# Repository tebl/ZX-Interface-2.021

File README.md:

# ZX Interface 2.021
I woke up in the middle of the night with idea, and like most non-sensical ideas - they usually disappear in the morning. Can't remember what that idea was, but it was properly better than this one: recreating a simple version of the *ZX Interface 2* because I simply can't afford the prices the original ones are going for. Having made a few *improvements* to the original design, I was going to call it the *ZX Interface 2000* - that would however imply that I had put anything modern into it, so *ZX Interface 2.021* was the name I came up with instead. There's even a short video showing it running on [YouTube](https://youtu.be/rGyqisjjOV8).

There are other more modern implementations for putting together a ZX Spectrum cartridge solution, the Dandanator comes to mind, but I wanted something without the magic black boxes (MCUs, FPGAs or GALs) - my goal is that it should be easy to build and easy to understand. Also, I kind of like having various physical cartridges that can plug into it - so an actual cartridge slot was always a requisite for this project. 

Over to the improvements then, of which there are mainly just one that hasn't already been mentioned (the first one being the elimination of custom IC, for which there are no replacements). The other one is that logic for bank switching has been integrated into the interface, in its current state it allows you to access up to 512k ROMs in 16k segments. Four of them actually, bringing the maximum addressable ROM up to a whopping 4MB (that's 4096KB, not merely 4 Mbit).

The cartridges available mostly will have some different attributes, so you'll need to check out the README for each one of them to access all relevant information. When starting out I recommend starting with the diagnostic cartridge, it supports a single EPROM of up to 64K - giving you access to four 16K ROM images that you can switch between by using a technique called [bank switching](https://github.com/tebl/ZX-Interface-2.021/blob/main/documentation/bank_switching.md). The ZX Spectrum computer doesn't exactly expect you to hot-swap them this way, so there is a need to add a [Cartridge Loader](https://github.com/tebl/ZX-Interface-2.021/tree/main/software/cartridge_loader) program to ensure that the program starts correctly. To make things a bit easier on myself when it comes to creating cartridge compilations, I've put together a [Cartridge Creator](https://github.com/tebl/ZX-Interface-2.021/tree/main/software/cartridge_creator) that automates tasks as well as supporting updating the loader program with bank titles as well as changing out the boot screen with ZX Spectrum SCR-files.

The diagnostic software I'm using by Brendan Alford, will attempt to write state information to the LEDs on port 63. You can also play around with them directly from basic, just do an "*OUT 63, 255*" - to turn all of them on. Battlestar Galactica fans will intuitively know what tomorrows project ought to be!

The project includes a bunch of faceplates, they are mainly just there to look incredibly cool! Especially in black. While I've done a few pretty ones to match specific games, I've not obtained permission to include the likeness of any of the characters - for that reason, those have been intentionally kept separate from the github-repository. They may however show up in the gallery sections, because they exist and I had fun making them for my own personal enjoyment.

## Getting one
I don't have the capability of selling completed units or "kits" for building one, mainly due to health reasons. If you want one you will probably have to build it yourself, alternatively you could always call your favourite friend - preferably one that already owns, or is willing to buy a soldering iron of reasonable quality.

The following table will point you to more information about the specific modules, including a list of the components that goes into building one of them (referred to as a BOM). While the interface can be used as a standalone Sinclair joystick interface, you'll more than likely want at least one of the additional cartridges so that you have something to plug into it as well. Note that there will be several faceplates available for these, these as well as the PCBs for the modules listed are available on [PCBWay shared projects](https://www.pcbway.com/project/shareproject/?tag=ZX%20Interface%202.021).

| Module                      | Description                       |
| --------------------------- | --------------------------------- |
| [ZX Interface 2.021](https://github.com/tebl/ZX-Interface-2.021/tree/main/ZX%20Interface%202021) | The actual interface, includes cartridge slot and joystick interface.
| [ZX Diagnostic 2.021](https://github.com/tebl/ZX-Interface-2.021/tree/main/ZX%20Diagnostic%202021) | A diagnostic cartridge, only for use with *ZX Interface 2.021*.
| [ZX Cartridge 2.021](https://github.com/tebl/ZX-Interface-2.021/tree/main/ZX%20Cartridge%202021) | Cartridge supporting up to two 64K ROMs, eight banks of data in total. Only for use with *ZX Interface 2.021*.
| [ZX Cartridge 1.983](https://github.com/tebl/ZX-Interface-2.021/tree/main/ZX%20Cartridge%201983) | A simple cartridge that can also be used with the original ZX Interface 2 (without bank switching support).

**NB!** As with all things you're soldering together by yourself, the one who soldered it - takes responsibility for it. I'll try to help in any way that I can, but know that this is a hobby-grade project and my health is not such that I can focus on too many things at any given time. Check out the [schematic](https://github.com/tebl/ZX-Interface-2.021/tree/main/documentation/schematic) while you wait, just about every problem is just an opportunity for learning and there is a significant chance that you'll be able to find your answer within it.

## Setting it up
The *ZX Interface 2.021* has a handful of jumpers that need to be set correctly in order to keep everything working as intended (refer to image below for reference). The jumper in the top left corner is used to enable the joystick interface, put a jumper across pins 1-2 (the lower position) and it should provide you with many hours of joy with your favourite Atari-compatible stick.

The second jumper, middle right section allows you to hardcode one of the address lines used for bank switching. Setting it the lower position forces it high, in effect allowing you to quickly select between two 16k ROM images in the first and second bank - when all else fails. This is here as a way to swap between diagnostic images when the machine isn't capabable of doing this in the preferred way. In normal use, jumper across pins 1-2 (this is the upper position).

**NB!** As with all kinds of vintage electronics that you don't want to destroy, you shouldn't attempt to insert or remove a cartridge when the system is powered up. Ignoring this will either kill this interface, the cartridge or your computer - sometimes all of them.

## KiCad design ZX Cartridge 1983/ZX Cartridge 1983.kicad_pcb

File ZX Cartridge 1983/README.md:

# ZX Cartridge 1.983
With the ZX Cartridge 2.021, I intentionally created a cartridge that wouldn't be compatible with any of the original cartridge interfaces released for the ZX Spectrum. The more known of these type of interfaces is the original *ZX Interface 2*, but Kempston also released a well known one in the form of the *Kempston Pro Joystick Interface*. The first one was naturally priced firmly out of my price-range, the second one I got a hold of wasn't in a working state - so I went for option three instead, the *RAM turbo Mk2* joystick interface. Having found a working interface, I wanted an actual cartridge to use with it - so I created the *ZX Cartridge 1.983* to test things out.

True to form, I didn't simply want to build a 16K cartridge - so I sprinkled a little bit of extra feature creep upon it. I figured that I'd look into being able to use even larger EEPROMs that what I'd used so far, with the 27C020 able to hold 16 of these images - pretty extreme when considering that the system only had 10 officially released titles. There are a few [cassette conversions](http://www.fruitcake.plus.com/Sinclair/Interface2/Cartridges/Interface2_RC_New_3rdParty_GameConversions.htm) that can be used as well, good enough to fill a couple of them. With 16 images possible combinations I needed a way to choose between them, cheap as I am the solution became a 4 position DIP-switch. Just because I already had them and the space, I added a completely optional HEX-decoder IC and 7segment display - gloriously over-engineered. Smaller (E)EPROMs can still be used such as the 27C256/27C512 can still be used, you just need to install components to match.

- [1> Building the cartridge](#1-building-the-cartridge)
  - [1.1> Soldering it together](#11-soldering-it-together)
  - [1.2> Testing it out](#12-testing-it-out)
- [2> Schematic](#2-schematic)
- [3> BOM](#3-bom)

# 1> Building the cartridge
Building the unit assumes you have at least minor experience soldering things together, recommended is at least a soldering station with adjustable temperature to get started - usually you'll want some 60/40 solder tin (if you can get that where you live). Given that we're going to be flashing data onto EPROM chips, you'll need an EPROM programmer suitable for this task - the one I'm using is a MiniPro TL866CS and so far it's surpassed my expectations for such a reasonably priced device. If you are going to use EPROM chips you will need an EPROM ereaser as well, but read on - you might not need that depending on the chips you purchase.

With the equipment sorted, now comes the shopping - so head on over to the [BOM](#3-bom)-section for some information on what you need. Note that with sites such as ebay, AliExpress and similar sites that sell cheap chinese components, you'll need to treat these as a suggested search term and look for something that matches the gallery pictures.

You'll need to order some EPROM chips as well. As previously mentioned, you can use anything from 27C128 up to 27C020 chips. One specific chip I can recommend looking for is the W27C512, W27C010 or W27C020 as that is actually an EEPROM with the compatible pin layouts, meaning you won't need the previously mentioned EPROM ereaser. The price difference should be negligible unless you're going to make a lot of them.

## 1.1> Soldering it together
The construction of this unit should be straight-forward, there's only a few components to speak of - and none of them overlap in any way. I do however recommend that you build up the components in increasing size, that way you'll have an easier time getting everything on there straight.

As shown above, we've started by installing resistors as well as the single diode (note the polarity marking, the line should match up with the board). Before moving onto anything else, we need to figure out which (E)EPROM chips we're going to install, for the two larger options we'll need to use a 32-pin socket (reconsider your life choices if not installing sockets) - for anything 27C512 or smaller we can use the common 28-variety, making sure that we leave a gap of four holes at the **top** of the board. Solder the jumper marked *ROM_TYPE* according to the table (the square pad marks pin 1, N/C means leave unconnected).

| (E)EPROM | ROM_SEL   | ROM_TYPE |
| -------- | --------- | -------- |
| 27C020   | 4 way DIP | 1-2      |
| 27C010   | 3 way DIP | N/C      |
| 27C512   | 2 way DIP | 2-3      |     
| 27C256   | 1 way DIP | 2-3      |
| 27C128   |           | 2-3      |     

The two capacitors aren't polarized, just get them stuck into the hole and you'll be ready to move along to a suitable beat. Next step is to put in the DIP-switches, but refer to the table above so that you use the correct one - mount it at the top, leaving empty holes towards the bottom of the board.

With the end of the build in sight, we focus on the single remaining component - the 7-segment display. The display should have be a 0.56" one, it should have been sold to you as one with a common cathodes (C.K.). If in doubt whether you have the correct display, put your multimeter in diode testing mode (oftenly referred to as *continuity*-mode) and ensure that you can light up one segment by putting the negative lead on the bottom center pin. Using the display requires an old IC marked MC14495P1, it is the only one I've come across that can count displays digits above 9 without costing an arm and a leg (I bought mine on AliExpress).

## 1.2> Testing it out
I shouldn't have to say it at this point, but I'll do so anyway - cartridges are not memory cards, plugging them in or unplugging them while the system is powered on will **KILL** your equipment. If you've not already done so, you'll need to put something on your selected (E)EPROM - see separate document on [flashing an EEPROM](https://github.com/tebl/ZX-Interface-2.021/blob/main/documentation/flash_eeprom.md) for details on how to do this (in particular the part on combining 16K images). With that out of the way, just plug the cartridge into the slot  and power on the ZX Spectrum.

One thing that I've found with ZX Spectrum cartridges is that they tend to restart when program running on it crashes, which we can at times use to simply move the switches to swap games. Not all of them will work reliably, but as with everything ZX Spectrum - if in doubt, just reset the computer and everything should be back to normal again. If you don't have a reset button available, such as when using the old interfaces on a non-plussed computer, you'd need pull the power - just like we did in 1983.

# 2> Schematic
The supplied KiCad files should be sufficient as both a schematic and as a  starting point for ordering PCBs (basically you could just zip the contents of the export folder and upload that on a fabrication site), the schematic is also available in [PDF-format](https://github.com/tebl/ZX-Interface-2.021/tree/main/documentation/schematic) and this is what you'll need to print and work your way through this things don't work as expected after assembly.

# 3> BOM
Most parts should be easy to get a hold of from your favourite local electronic component shop, but given that I don't have access to such shops where I live so everything was based on whatever I could get cheapest from eBay/AliExpress (free shipping, but plan on waiting 3-4 weeks for delivery). 

| Reference             | Item                                                              | Count | Order  |
| --------------------- | ----------------------------------------------------------------- | ----- | ------ |
| Cartridge PCB         | Fabricate using Gerber files                                      |     1 | [PCBWay]()
| AFF1 *                | 0.56" 7-segment display (C.K.)                                    |    (1)|
| C1,C2                 | 100nF ceramic capacitor (5mm pin spacing)                         |  1 (1)|
| D1                    | 1N4148 small signal diode (DO-35)                                 |     1 | 
| R1                    | 680 ohm resistor                                                  |     1 |
| R2-R5                 | 4k7 (4700) ohm resistor                                           |     4 |
| U1 **                 | 27C020 or smaller (E)EPROM (W27C020 recommended)                  |     1 |
| U1 *                  | MC14495P1 (DIP-16)                                                |    (1)|
| SW1 **                | 1-4 way DIP switch                                                |     1 |
| Mounting ***          | Nylon M3 hex standoffs 8mm                                        |    (4)|
| Mounting ***          | Nylon M3x6mm nylon screws                                         |    (4)|
| Mounting ***          | M3 nylon nut                                                      |    (4)|  

*) These are optional components that are just used to show the slot number. Cool, but not needed.

**) The DIP switch needs to match the size of the (E)EPROM that you wish to install on the board, for more information have a read-through of [1.1> Soldering it together](#11-soldering-it-together).

***) The easiest way of ordering these is to just one of the M3 nylon standoff kits on ebay, AliExpress or any similar sites. That way you'll get more than what you need in various sizes for future projects as well. Check out [faceplate](https://github.com/tebl/ZX-Interface-2.021/tree/main/faceplates) section of this repository or [PCBWay shared projects](https://www.pcbway.com/project/shareproject/?tag=ZX%20Interface%202.021) for available options.

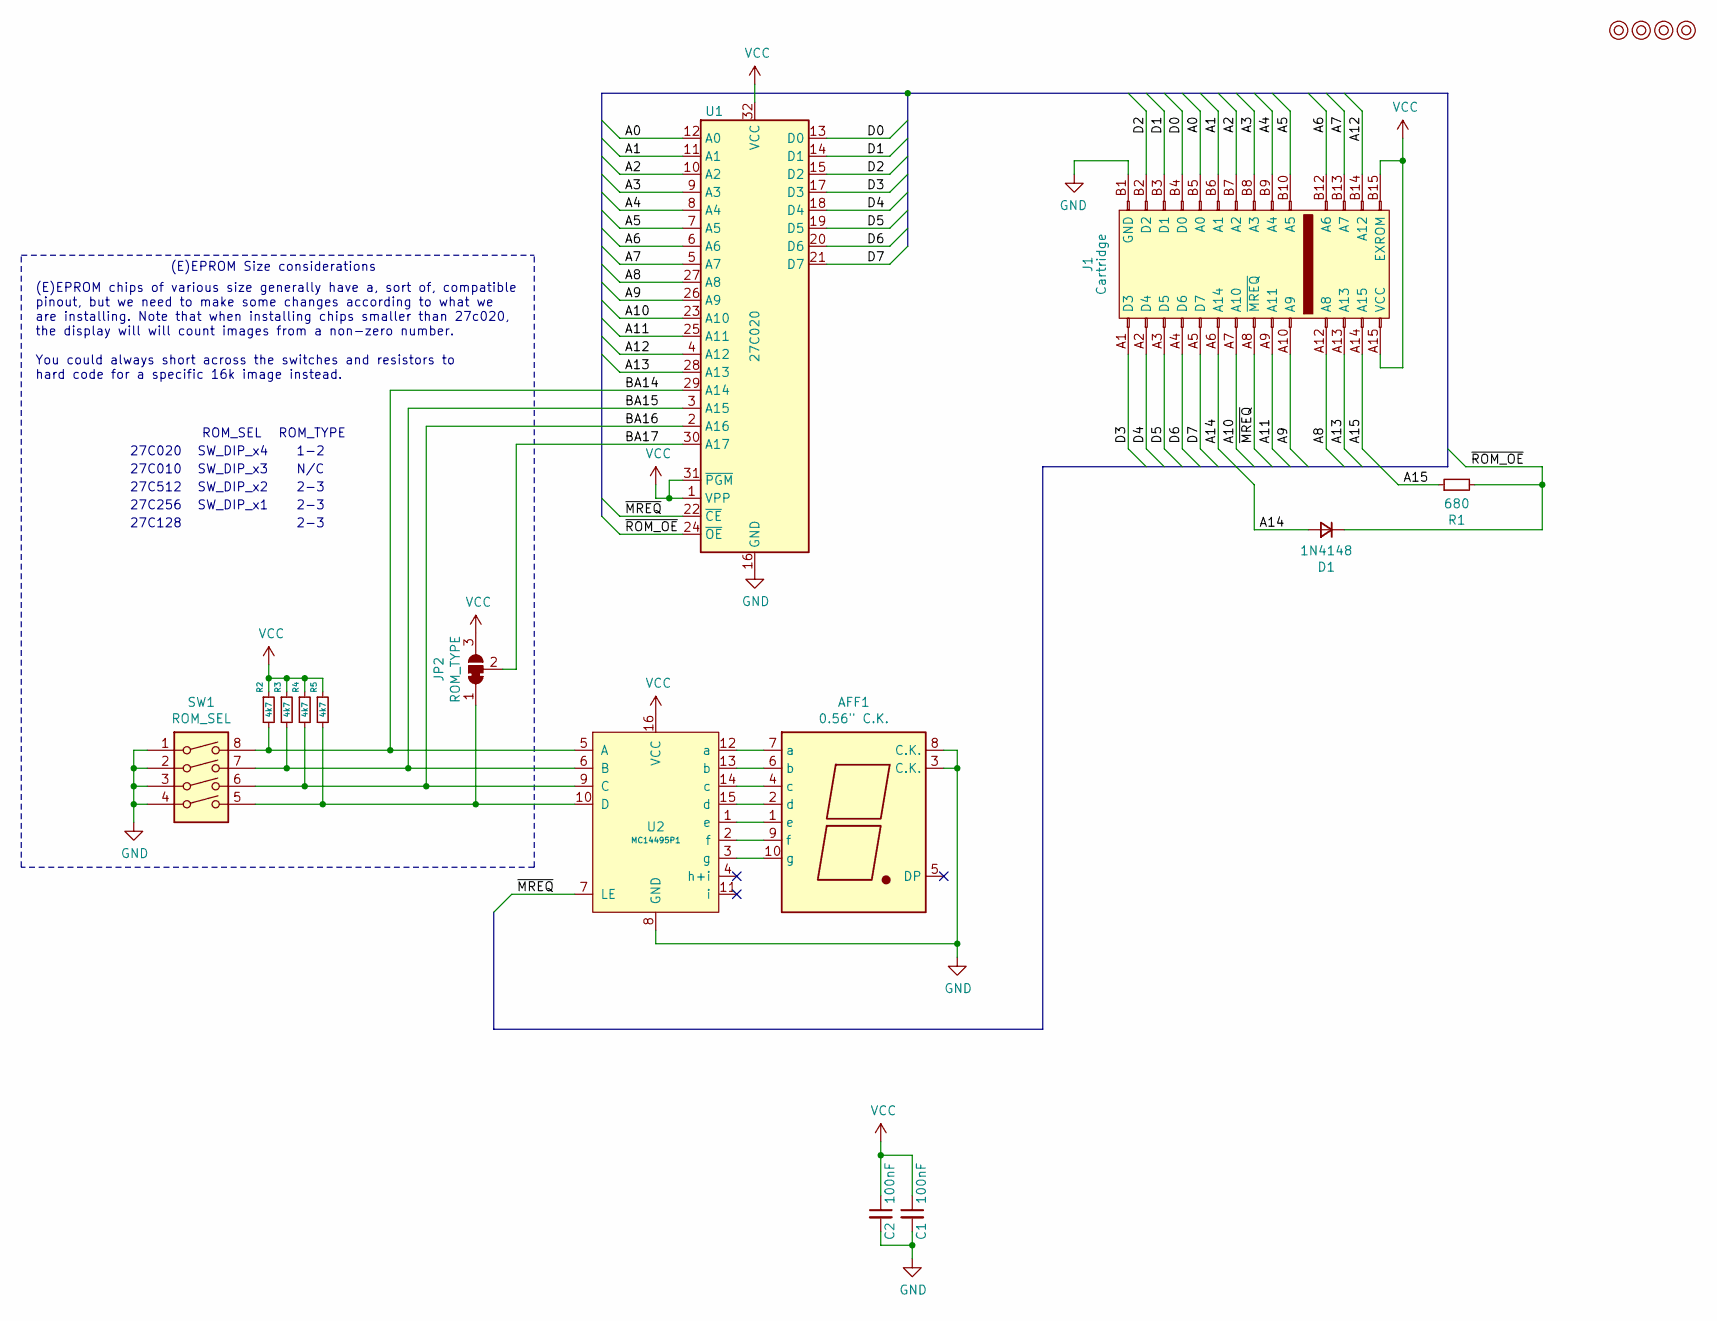
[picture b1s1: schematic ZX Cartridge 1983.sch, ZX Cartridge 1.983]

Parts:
AFF1: 0.56\" C.K.; 7SegmentLED_LTS6760_LTS6780
C1, C2: 100nF; C_Disc_D4.7mm_W2.5mm_P5.00mm
D1: 1N4148; D_DO-35_SOD27_P7.62mm_Horizontal
J1: Cartridge; ZX_Spectrum_Cartridge_Original
JP2: ROM_TYPE; select
M1, M2, M3, M4: Mounting; M3_pin
R1: 680; R_Axial_DIN0207_L6.3mm_D2.5mm_P10.16mm_Horizontal
R2, R3, R4, R5: 4k7; R_Axial_DIN0207_L6.3mm_D2.5mm_P7.62mm_Horizontal
SW1: ROM_SEL; SW_DIP_SPSTx04_Slide_9.78x12.34mm_W7.62mm_P2.54mm
U1: 27C020; DIP-32_W15.24mm_Socket_LongPads
U2: MC14495P1; DIP-16_W7.62mm_Socket_LongPads

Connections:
/A0: J1.B5 (A0), U1.12 (A0)
/A1: J1.B6 (A1), U1.11 (A1)
/A2: J1.B7 (A2), U1.10 (A2)
/A3: J1.B8 (A3), U1.9 (A3)
/A4: J1.B9 (A4), U1.8 (A4)
/A5: J1.B10 (A5), U1.7 (A5)
/A6: J1.B12 (A6), U1.6 (A6)
/A7: J1.B13 (A7), U1.5 (A7)
/A8: J1.A12 (A8), U1.27 (A8)
/A9: J1.A10 (A9), U1.26 (A9)
/A10: J1.A7 (A10), U1.23 (A10)
/A11: J1.A9 (A11), U1.25 (A11)
/A12: J1.B14 (A12), U1.4 (A12)
/A13: J1.A13, U1.28 (A13)
/A14: D1.2 (A), J1.A6 (A14)
/A15: J1.A14 (A15), R1.1
/BA14: R2.2, SW1.8, U1.29 (A14), U2.5 (A)
/BA15: R3.2, SW1.7, U1.3 (A15), U2.6 (B)
/BA16: R4.2, SW1.6, U1.2 (A16), U2.9 (C)
/BA17: JP2.2 (C), U1.30 (A17)
/D0: J1.B4 (D0), U1.13 (D0)
/D1: J1.B3 (D1), U1.14 (D1)
/D2: J1.B2 (D2), U1.15 (D2)
/D3: J1.A1 (D3), U1.17 (D3)
/D4: J1.A2 (D4), U1.18 (D4)
/D5: J1.A3 (D5), U1.19 (D5)
/D6: J1.A4 (D6), U1.20 (D6)
/D7: J1.A5 (D7), U1.21 (D7)
/~MREQ: J1.A8 (~MREQ), U1.22 (~CE), U2.7 (LE)
/~ROM_OE: D1.1 (K), R1.2, U1.24 (~OE)
GND: AFF1.3 (C.K.), AFF1.8 (C.K.), C1.2, C2.2, J1.B1 (GND), SW1.1, SW1.2, SW1.3, SW1.4, U1.16 (GND), U2.8 (GND)
unnamed: AFF1.1 (e), U2.1 (e)
unnamed: AFF1.2 (d), U2.15 (d)
unnamed: AFF1.4 (c), U2.14 (c)
unnamed: AFF1.6 (b), U2.13 (b)
unnamed: AFF1.7 (a), U2.12 (a)
unnamed: AFF1.9 (f), U2.2 (f)
unnamed: AFF1.10 (g), U2.3 (g)
unnamed: JP2.1 (A), R5.2, SW1.5, U2.10 (D)
VCC: C1.1, C2.1, J1.A15 (VCC), J1.B15 (EXROM), JP2.3 (B), R2.1, R3.1, R4.1, R5.1, U1.1 (VPP), U1.31 (~PGM), U1.32 (VCC), U2.16 (VCC)

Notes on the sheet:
27C512
27C256
27C128
2-3
(E)EPROM Size considerations
(E)EPROM chips of various size generally have a, sort of, compatible pinout, but we need to make some changes according to what we are installing. Note that when installing chips smaller than 27c020, the display will will count images from a non-zero number. You could always short across the switch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
27C010
SW_DIP_x3
SW_DIP_x2
SW_DIP_x1
27C020
ROM_SEL
SW_DIP_x4
ROM_TYPE
1-2
N/C

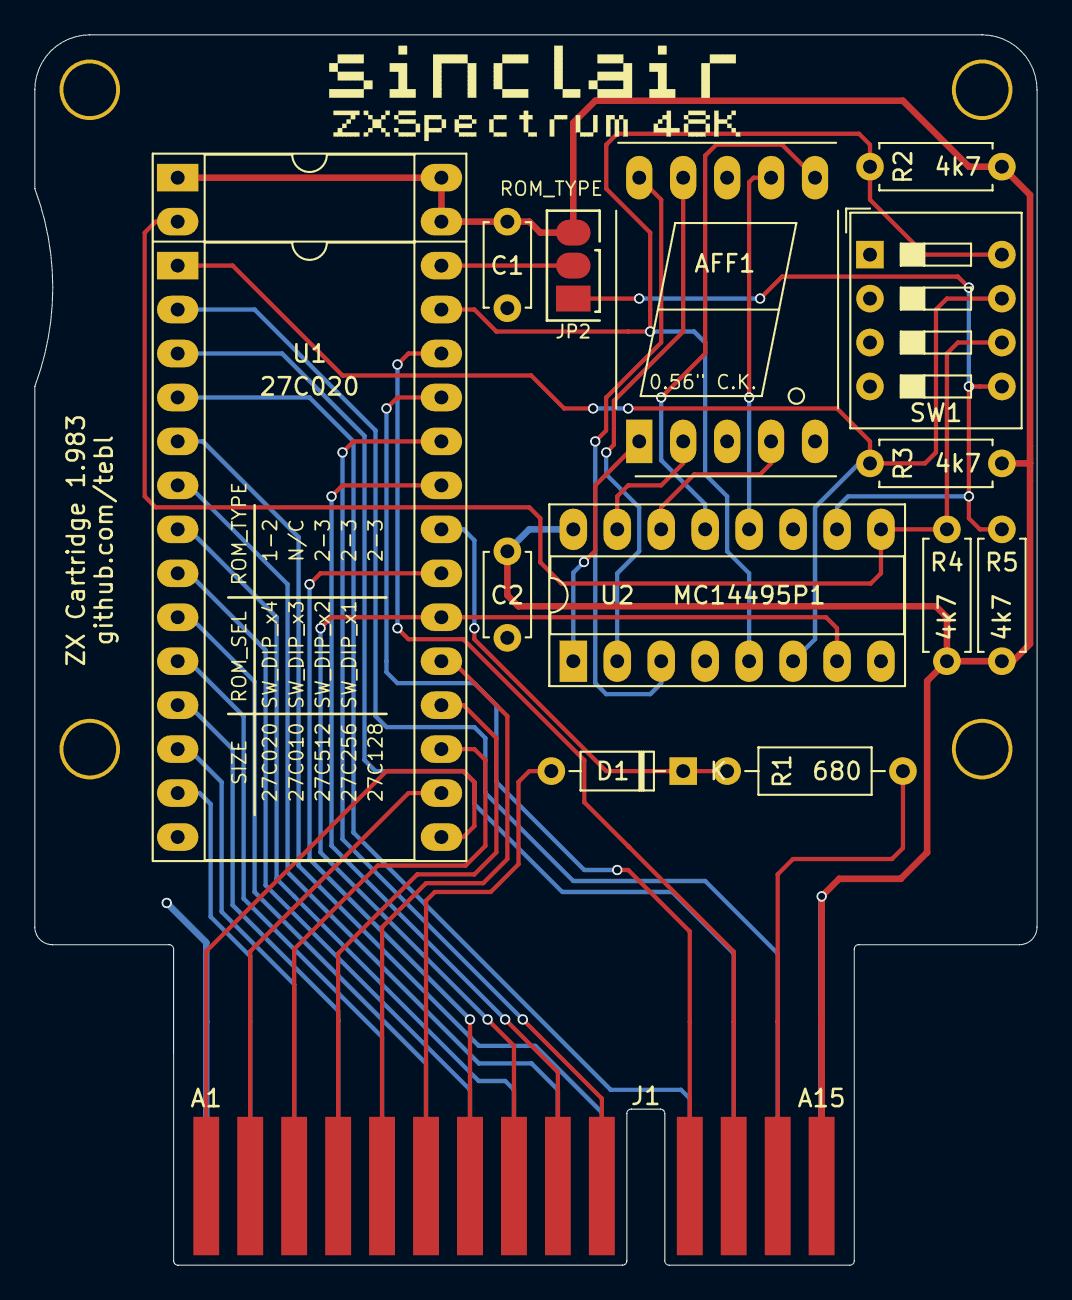
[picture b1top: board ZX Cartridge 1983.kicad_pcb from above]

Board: 2 copper layers, 57.9 x 71.1 mm, 19 parts (0 on the bottom side), 40 nets.

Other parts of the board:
sinclair_title: sinclair_title

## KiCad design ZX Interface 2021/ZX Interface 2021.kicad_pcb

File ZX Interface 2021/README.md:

# ZX Interface 2.021
This is the module that the project is named after, the actual implementation of the the *ZX Interface 2.021*. Part of the hardware used within the *ZX Interface 2.021* has been designed to be functionally similar to available diagnostic cartridges, but I've also added a Sinclair joystick interface that should functionally work the same way as the original *ZX Interface 2*. 

While the original interface only supported 16K cartridges, severely limiting the amount of titles that could have been released for it, I didn't want to design a new interface without addressing those shortcomings. This was solved by adding a new section of pins to the end of the cartridge - these'll probably get in the way of original cartridges, but I can't afford any of those so unless someone straight-up sends me some I can't design anything for them. In theory, it should work without any changes.

Note that there are various faceplates available for the interface as well as the cartridges, these complete the look as well as add some sturdyness to the design. Check out the [faceplates](https://github.com/tebl/ZX-Interface-2.021/tree/main/faceplates) section for an overview over the ones that have been made available, also see [PCBWay shared projects](https://www.pcbway.com/project/shareproject/?tag=ZX%20Interface%202.021).

- [1> Building the interface](#1-building-the-interface)
  - [1.1> Soldering it together](#11-soldering-it-together)
  - [1.2> Card edge connectors](#12-card-edge-connectors)
  - [1.3> Assembling the unit](#13-assembling-the-unit)
  - [1.4> Testing it out](#14-testing-it-out)
- [2> Schematic](#2-schematic)
- [3> BOM](#3-bom)

# 1> Building the interface
Building an interface such as this assumes you have at least minor experience soldering things together, recommended is that you at least have access to a soldering station with adjustable temperature - if you can get it, you should probably start with 60/40 solder tin as the lead-free alternatives tends to be harder to work with though it's certainly a category that can be considered too cheap.

With the equipment sorted, now comes the shopping - so head on over to the [BOM](#3-bom)-section for some information on what you need. Note that with sites such as ebay, AliExpress and similar sites that sell cheap chinese components, you'll need to treat these as a suggested search term and look for something that matches the gallery pictures.

This document will only cover the actual interface, there are separate documents for the various cartridges available - at a minimum I recommend starting with the *ZX Diagnostic 2.021*, it has a few extra features that you can easily have silly amounts of fun with.

## 1.1> Soldering it together
The construction of this unit should be fairly straight-forward, just take your time in order to make sure everything goes into place - more or less straight. I usually recommend starting by having a good look at the PCBs, try to figure out where all of the listed components go and in which orientation they go in (all of this should be clearly marked on the silkscreen). 

I will usually try to install components sorted by their physical size, doing it this way means you'll have an easier time keeping everything from looking somewhat crooked. This is your board, your build and you want it perfect - don't you? If you said no, then go sit in the corner because I worked hard creating this for myself and whoever wants one.

Here we've started by soldering all of the resistors, ensuring that we're using the correct values in each position. The diodes are installed similarly, but these have a polarity and so you need to install these correctly by matching up the stripe with the stripe as shown on the silkscreen.

Moving things along, we've added the right-angle pin header - soldering one pin into place, then reheating and adjusting it's position so that it looks straight before soldering the rest of the pins. The sockets have been installed as well, here we've taken care to match up the indent in the socket as shown on the silkscreen - pins 1 on all of the ICs here will therefore be found on the lower-left corner. I recommend soldering in each of the corners on the sockets, but before soldering the rest - check that they're still sitting flush against the board.

The capacitors used on this board are mainly non-polarized, these are the small yellow ones found next to the IC-sockets and these are quickly soldered into place. The electrolytic marked C5 on the other hand needs to be installed the correct way - the longer lead goes into the lower hole marked with a "*+*". Don't solder that into place yet though, you need to measure the height of the component first as we will only have space for one that is at most 8mm tall - if the ones you have are longer, you'll need to install it on it's side instead.

Here, the LED have been added to the PCB. These also have a specific orientation that you need to install it in, but to keep things short without actually using any of the correct terms - just put the longer lead into the round hole. Solder one of the pins into place first, then reheat and push it firmly against the board before soldering in the remaining lead. We need this to line up with the faceplate that goes on top, so you need to aim straight here. Given that this is your new power LED, this will always be lit when the computer is on - so pick a colour you find comfortable to look at (preferably not one of those awful super-bright blue ones).

At this point we'll be jumping a bit ahead in the build, mainly because there are a few components that we need to ensure will match the cutouts on the faceplate. So here I've gone ahead and soldered in the two switches, choosing something that's long enough to poke through the faceplate so that you can actually push them (or not, in case you want to force yourself to use a sharpie to push them instead). The DB9-connectors I've just screwed onto the main PCB by using longer M3 nylon screws through eight M3 nylon nuts, through the board and finally adding four more M3 nylon nuts to the underside of the board.

Now it's time to the install the card edge connectors that connects to the actual ZX Spectrum computer, but we'll need to cut it down for size and add a nail through it to add some keying. Given that doing this is an entirely different project by itself, at least when you're doing it for the first time - you'll find all of the details in [1.2> Card edge connectors](#12-card-edge-connectors), then come back here for the exciting continuation of this project.

Start by soldering the component, aligning the pins to the underside of the PCB without bending them in any way - keep them straight and take care that you install the keyed part with the section marked *SLOT* on the PCB. When it looks straight enough, solder in two of the opposing corners before doing the rest. At this point you need to check that the slot isn't at an angle, but looks to be parallell to the PCB. When satisfied continue soldering the rest of the pins on the underside.

Now it's time to deal with the pins on the topside of the PCB. There are no correct way to install it as the part really has pins that are too short, but I thing you'll get the strongest joint when the pins have been bent into an L-shape like in the picture. You can easily get this shape by taking a flat-bladed screwdriver, place it onto the center of the pin and pushing it down until you get the desirable shape as you can see in the picture above. When done, recheck that the connector still is parallel to the main PCB - bend it slightly if not. Solder everything into place, as long as you don't bridge anything onto the next pin I recommend adding a *LOT* to give it some added strength.

The last of the big components to go into place is the cartridge connector, as with the other connector we'll need to match up the areas marked *SLOT* with the keying added. You should already have checked out [1.2> Card edge connectors](#12-card-edge-connectors), where I went into detail on how the keying part is done. Solder it into place. If you haven't already soldered the DB9-connectors into place, feel free to do so after testing that the alignment will fit snuggly with the faceplate.

Finally, we're ready to add the jumper caps to the board as shown above - the joystick enable jumper must be in the lower position (across pins 1-2) for the Sinclair joystick interface to work. The other jumper should be kept in the upper position, this can be used to select between the two lower ROM banks of the inserted cartridge - the idea here was that with a non-functional computer you could use this to swap between two diagnostic ROMs. The various ICs have also been inserted into the sockets, taking care to match up the indented part of the chip with the socket as well as the silkscreen underneath.

At this point you should be ready to skip forward to section [1.3> Assembling the unit](#13-assembling-the-unit), mainly as we've already done everything that was described in section [1.2> Card edge connectors](#12-card-edge-connector) at an earlier stage.

## 1.2> Card edge connectors
The card edge connectors used with the *ZX Interface 2.021* widely vary in terms of quality, especially those sold from sites that primarily sell Chinese components tend to be somewhat weak. If you want one that is of a better quality, you can usually get them ready-made from Ben Versteeg at [bytedelight.com](https://www.bytedelight.com/?product=edge-connector-ready-for-zx-spectrum-a-brand). The cheaper ones are however the ones I have, so these are the ones you'll find in the pictures. If you intend to sell a completed unit to someone else, you'll probably need to look for one for sale at a more reputable electronics shop such as mouser etc.

Cheap or expensive, unless you bought some that have already been adapted for use - we'll need to make some changes to them. If you find an ebay seller that describes them as *uncut* ZX Spectrum edge connectors, you're getting the cheap ones at a higher price - you'll still need to follow the rest of this section to adapt them for use. For the computer-side of the interface, we'll need to cut down on the width of the connector as well as add keying to it.

Starting with the ones that plug into the ZX Spectrum computer, you'll quickly find that these are a bit too wide to actually fit the computer. At this point you'll need some sort of fine-toothed saw, I simply can't recommend attempting to chew it off - they taste rather *industrial*. A vise such as the one shown above will help quite a bit if you have one, but you could always try holding it in place. Where exactly to cut? Well, notice the little nubs on the underside of the component? Just align your saw with the inner side of these and cut straight down through the plastic, use some sanding paper or a file to clean up the edges.

This connector, as well as the cartridge slot, will require some sort of keying - this ensures that the pins line up perfectly, or at least close enough that we don't accidentally short the wrong things. These are marked on the PCB as *SLOT*, the classic way of adding them is using nails. Not even kidding, I'm totally serious.

Start by removing the copper spring from that area, just push the pin upwards from the underside of the connector, then pull them out from the top. For the next step I recommend finding an extremely small drill, it needs to be smaller than the nail you want to use and then drill a hole along the top of the connector - leaving enough space that the nail won't simply be pulled through the plastic.

Take your selected nail, making sure that it's not a ridiculously big one or made super-strong so that you can't cut it - think of those super-cheap ones you get with IKEA furniture, these are ones you're looking for. Push it through the holes you drilled. In order to get the head flush with the plastic, I tend to use my soldering iron to push it slightly into the plastic - this'll also ensure that it won't be going anywhere soon. Use a strong pair of pliers to cut off the remainder of the nail from the other side, try to get it as close to the plastic as you can to avoid scratching up your desk or ZX Spectrum case too much.

That should be it, remember that the cartridge slot will have two keying pins that you need to add, but at least you won't have to cut the actual connector. When finished, get back to section [1.1> Soldering it together](#11-soldering-it-together) to finish building the actual interface.

## 1.3> Assembling the unit
There isn't all that much that can be said for assembling the unit, chances are you've already finished the entire thing by this point - test-fitting as you went along with it. A [faceplate](https://github.com/tebl/ZX-Interface-2.021/tree/main/faceplates) might not be a requirement for building a functional interface, but it is highly recommend that you get it -  it helps keep the cartridge from flopping around in the cartridge slot. Not to mention the added visual flair!

The suggested way of attaching the faceplate is by using 8mm tall nylon hex standoffs between it and the main PCB, adding M3 screws from the top to fit it firmly into place. The middle section can be of the F-F kind, but the M-F will also work here. The most important part is that you need 6mm tall M3 nylon standoffs to the bottom of the PCB, this should ensure that the interface lines up with your desktop surface while plugged into ZX Spectrum computer without wobbling around - refer to the image above to see how they're assembled (just don't over-tighten them like I did).

## 1.4> Testing it out
I shouldn't have to say it at this point, but I'll do so anyway - cartridges are not memory cards, plugging them in or unplugging them while the system is powered on will **KILL** your equipment. With that out of the way, just plug any suitable cartridge into the slot and then apply power to see if whatever you put into the first 16K of the (E)EPROM comes up as expected.

With the interface connected to your ZX Spectrum computer, but no cartridge inserted - the computer should boot into ZX Basic as normal. If it doesnt't then quickly disconnect it as something will have gone wrong with the build, you should attempt to figure out what that is before powering it up again. Try comparing your built unit to the pictures earlier in this document, pay particular attention to the components that need to be installed in a specific way - especially the diodes, the transistor and the various ICs all have a specific orientation that they need to be installed in.

If it boots as normal, then you can test out the joystick interface - simply by plugging in an Atari-style joystick into any of the ports and you should get characters printed on the screen when any of the directions or the button is pushed.

When you're ready to plug in a cartridge, remember to unplug the power to the computer - now that we've added that fancy new power LED, this should be easy to remember so unplug the bleeping thing. Ahem... now just plug in a cartridge you've previously built, it should start up whatever has been added as the first data bank on the inserted cartridge. This could be a a game, a diagnostic program, which was badly photographed above, or even a complete replacement for the ZX Basic.

If you want to access something in the other banks, you'll at least need a basic or some other kind of selector program in the first bank - these are all details I've attempted to describe in a separate document named [bank_switching](https://github.com/tebl/ZX-Interface-2.021/blob/main/documentation/bank_switching.md). For more information, also see the README that comes with each of the cartridges.

# 2> Schematic
The supplied KiCad files should be sufficient as both a schematic and as a  starting point for ordering PCBs (basically you could just zip the contents of the export folder and upload that on a fabrication site), the schematic is also available in [PDF-format](https://github.com/tebl/ZX-Interface-2.021/tree/main/documentation/schematic) and this is what you'll need to print and work your way through this things don't work as expected after assembly.

# 3> BOM
Most parts should be easy to get a hold of from your favourite local electronic component shop, but given that I don't have access to such shops where I live so everything was based on whatever I could get cheapest from eBay/AliExpress (free shipping, but plan on waiting 3-4 weeks for delivery). Components in parenthesis can be considered optional to enable basic functionality, but where's the fun in that? You deserve the complete package.

| Reference             | Item                                                              | Count | Order  |
| --------------------- | ----------------------------------------------------------------- | ----- | ------ |
| Interface PCB         | Fabricate using Gerber files                                      |     1 | [PCBWay](https://www.pcbway.com/project/shareproject/ZX_Interface_2_021.html)
| Faceplate PCB *       | Fabricate using Gerber files                                      |    (1)| [PCBWay](https://www.pcbway.com/project/shareproject/ZX_Interface_2_021__Faceplate_FA1_.html)
| C1-C4,C6-C8           | 100nF ceramic capacitor (5mm pin spacing)                         |     6 |
| C5                    | 10uF 25v electrolytic capacitor (2mm pin spacing)                 |    (1)|
| D11                   | 5mm LED, preferably one that is frosted                           |     1 |
| D1-D10,D12-D16        | 1N4148 small signal diode (DO-35)                                 |    15 | 
| J1,J2                 | D-SUB 9 Pin Male straight round pin PCB connector                 |     2 |
| J3                    | 3pin right-angle pin-header (with jumper cap)                     |     1 |
| J4                    | Industrial Card Edge Slot Socket Connector 22x2P 44P 2.54mm 0.1"  |     1 |
| J5                    | 3pin straight pin-header (with jumper cap)                        |     1 |
| Q1                    | 2N3904 transistor (TO-92)                                         |     1 |
| R1-R5,R12             | 10k ohm resistor                                                  |     6 |
| R11,R13               | 1k ohm resistor                                                   |     2 |
| R14                   | 330 ohm resistor                                                  |     1 |
| R15                   | 20k ohm resistor                                                  |     1 |
| SW1,SW2               | 6x6x9mm momentary switch                                          |     2 |
| U1,U2                 | 74LS245 (DIP-20)                                                  |     2 |
| U3                    | 74LS27 (DIP-14)                                                   |     1 |
| U4                    | 74LS04 (DIP-14)                                                   |     1 |
| U6                    | 74LS273 (DIP-20)                                                  |     1 |
| U7,U8                 | 74LS138 (DIP-14)                                                  |     2 |
| Z1                    | Industrial Card Edge Slot Socket Connector 28x2P 56P 2.54mm 0.1"  |     1 |
| Metal nails           | Small metal nails used for keying edge connectors                 |     3 |
| Mounting **           | Nylon M3 hex standoffs 6mm (F-F)                                  |     6 |
| Mounting **           | Nylon M3 hex standoffs 8mm (M-F)                                  |    (6)|
| Mounting **           | Nylon M3x6mm nylon screws                                         |     6 |
| Mounting ***          | Nylon M3x10mm nylon screws                                        |    (4)|
| Mounting ***          | M3 nylon nut                                                      |   (12)|  

*) Check out [faceplate](https://github.com/tebl/ZX-Interface-2.021/tree/main/faceplates) section of this repository or [PCBWay shared projects](https://www.pcbway.com/project/shareproject/?tag=ZX%20Interface%202.021) for available options. The default one will be linked as the order URL.

**) These are used in various places of the project. You can usually find some kits for M3 nylon standoffs, but given the amounts we're using - it's a good idea to order extras as well. The F-F variants won't be included with the tip, but with some creative cutting and combining things you should be able to achieve the same results - the important part is the heights between the components. When not installing a faceplates you'll be able to save on these, just keep the 6mm tall standoffs on the bottom.

***) These are used when bolting the DB9 connectors to the PCB - you can do without them, but in order to reduce the wear and tear on the main PCB I recommend installing them. You can't add these after the DB9-connectors have been soldered into place, at least not easily.

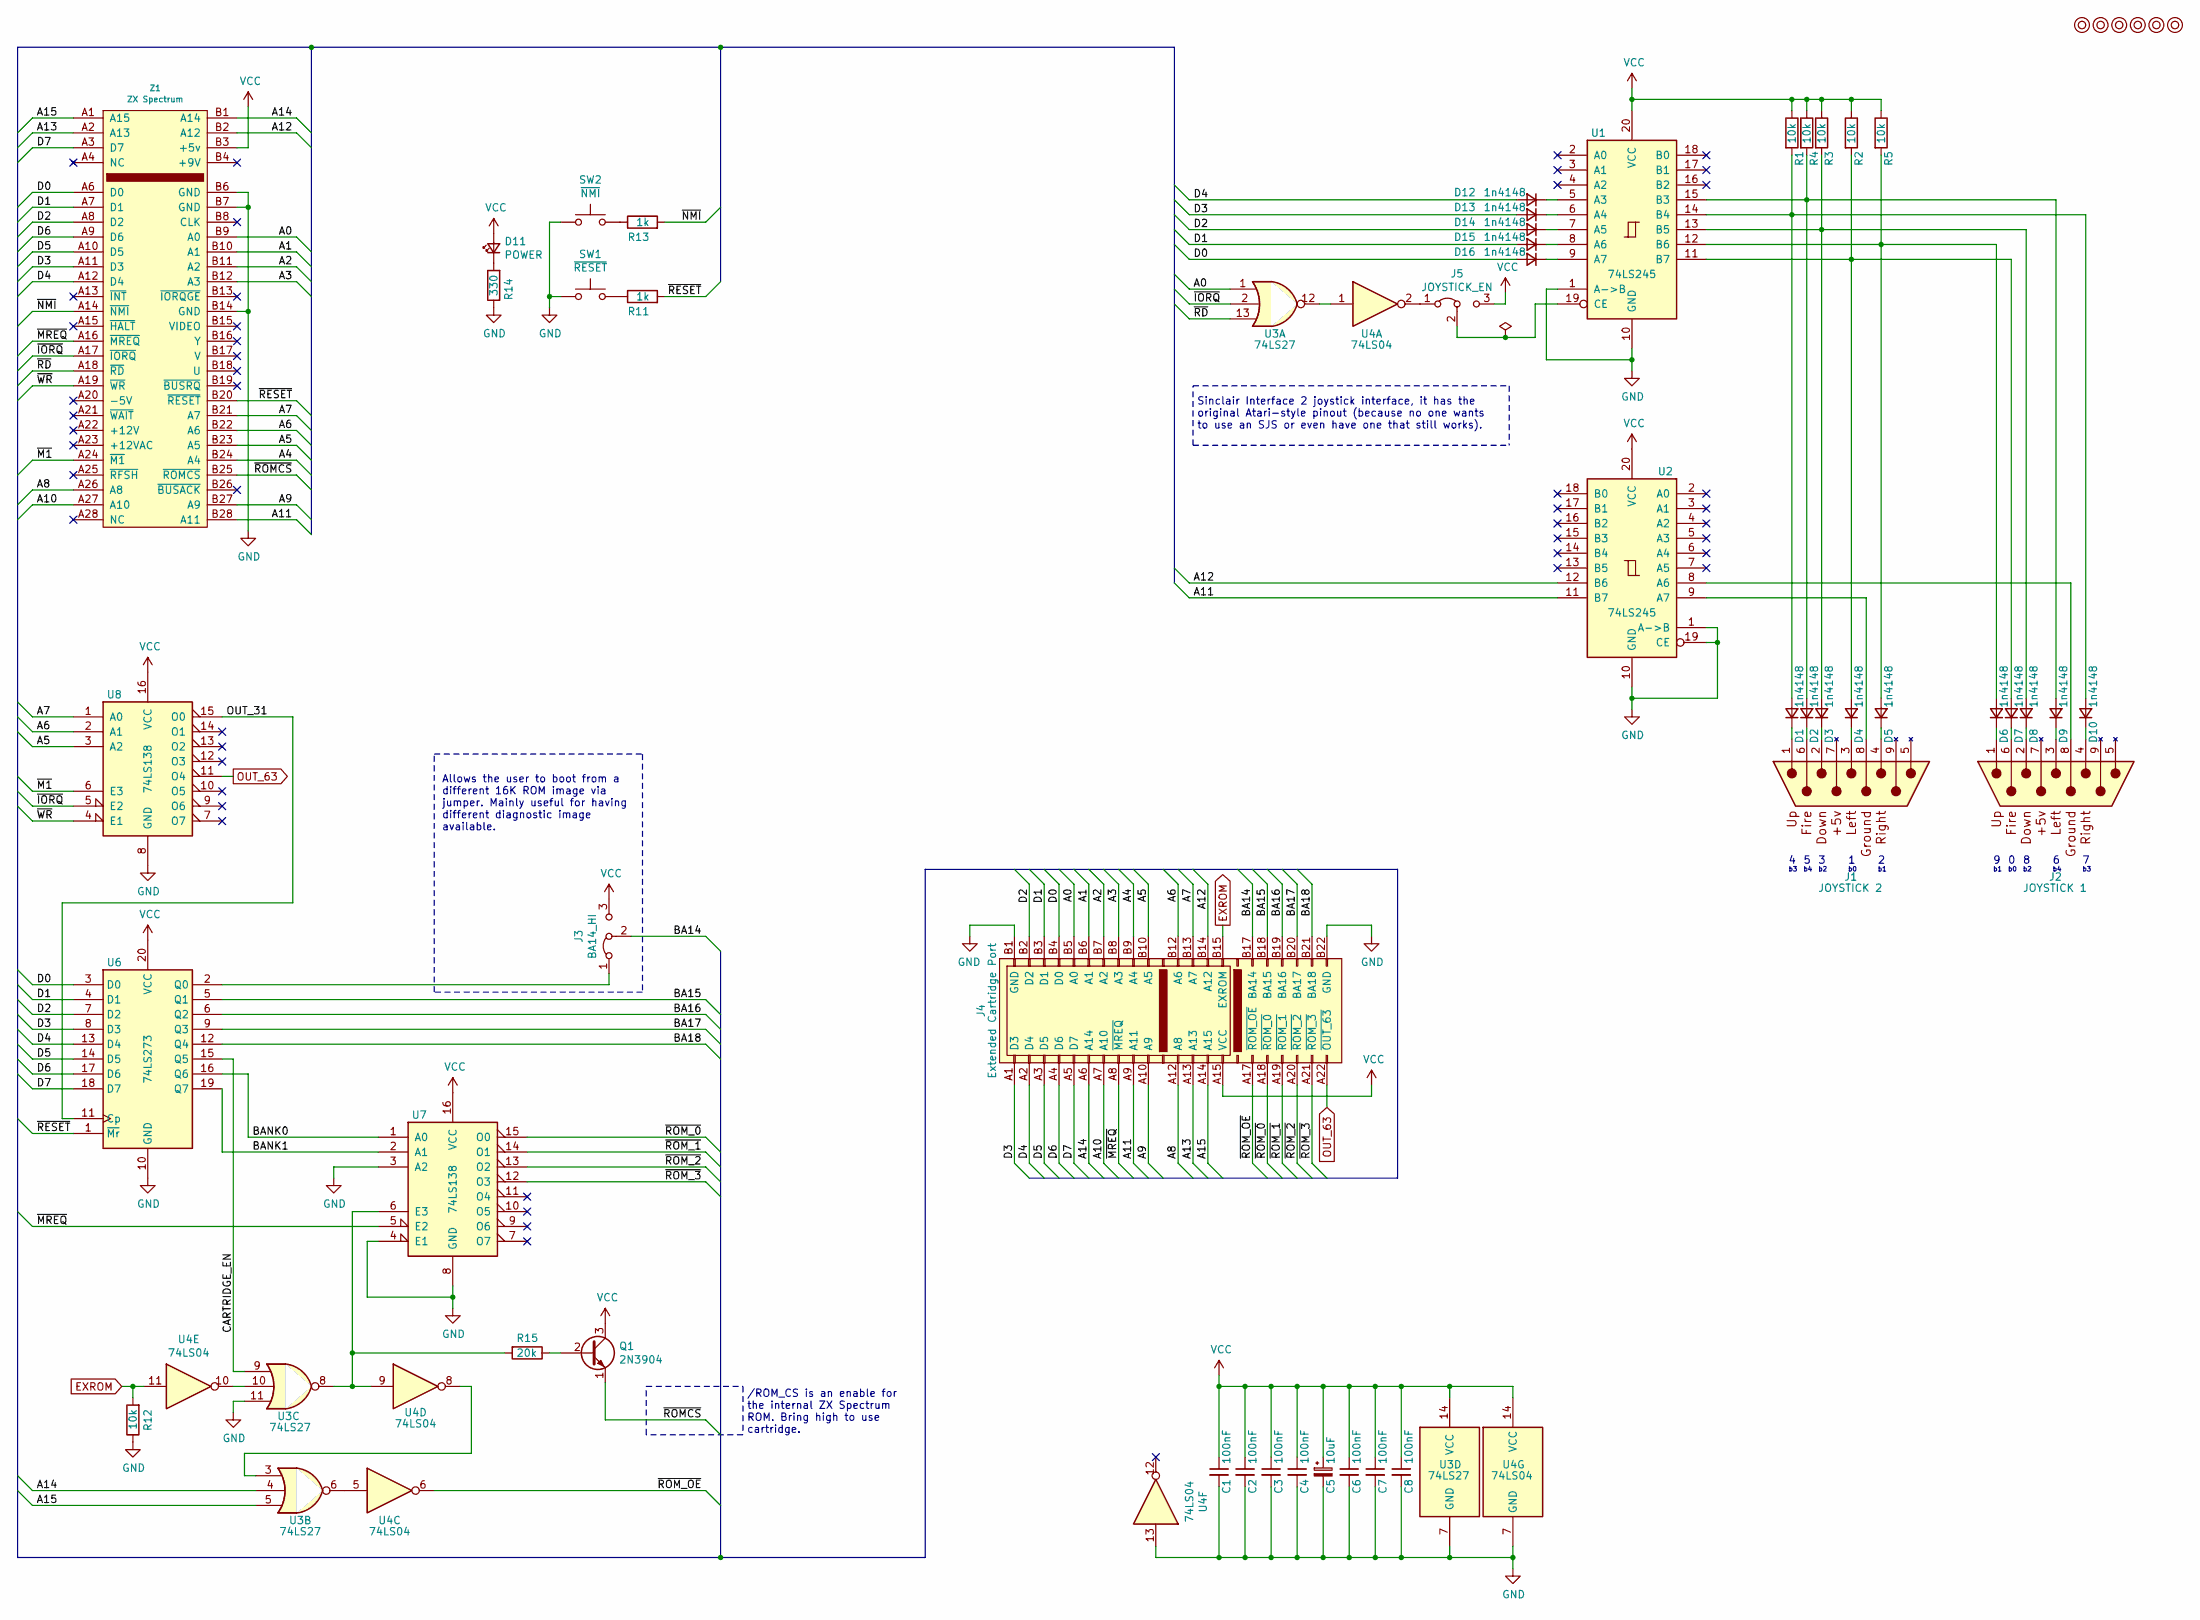
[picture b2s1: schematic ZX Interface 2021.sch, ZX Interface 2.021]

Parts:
C1, C2, C3, C4, C6, C7, C8: 100nF; C_Disc_D4.7mm_W2.5mm_P5.00mm
C5: 10uF; C_Radial_D4.0mm_H7.0mm_P1.50mm
D1, D2, D3, D4, D5, D6, D7, D8, D9, D10, D12, D13, D14, D15, D16: 1n4148; D_DO-35_SOD27_P7.62mm_Horizontal
D11: POWER; LED_D5.0mm
J1: JOYSTICK 2; DSUB-9_Male_Vertical_Pitch2.77x2.84mm
J2: JOYSTICK 1; DSUB-9_Male_Vertical_Pitch2.77x2.84mm
J3: BA14_HI; PinHeader_1x03_P2.54mm_Horizontal
J4: Extended Cartridge Port; ZX_Spectrum_Cartridge_Port
J5: JOYSTICK_EN; PinHeader_1x03_P2.54mm_Vertical
M1, M2, M3, M4, M5, M6: Mounting; M3_pin
Q1: 2N3904; TO-92_Inline_Wide
R1, R2, R3, R4, R5, R12: 10k; R_Axial_DIN0207_L6.3mm_D2.5mm_P10.16mm_Horizontal
R11, R13: 1k; R_Axial_DIN0207_L6.3mm_D2.5mm_P10.16mm_Horizontal
R14: 330; R_Axial_DIN0207_L6.3mm_D2.5mm_P10.16mm_Horizontal
R15: 20k; R_Axial_DIN0207_L6.3mm_D2.5mm_P10.16mm_Horizontal
SW1: ~RESET; SW_PUSH_6mm
SW2: ~NMI; SW_PUSH_6mm
U1, U2: 74LS245; DIP-20_W7.62mm_Socket_LongPads
U3: 74LS27; DIP-14_W7.62mm_Socket_LongPads
U4: 74LS04; DIP-14_W7.62mm_Socket_LongPads
U6: 74LS273; DIP-20_W7.62mm_Socket_LongPads
U7, U8: 74LS138; DIP-16_W7.62mm_Socket_LongPads
Z1: ZX Spectrum; ZX_Spectrum_Expansion_Edge

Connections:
/A0: J4.B5 (A0), U3.1, Z1.B9 (A0)
/A1: J4.B6 (A1), Z1.B10 (A1)
/A2: J4.B7 (A2), Z1.B11 (A2)
/A3: J4.B8 (A3), Z1.B12 (A3)
/A4: J4.B9 (A4), Z1.B24 (A4)
/A5: J4.B10 (A5), U8.3 (A2), Z1.B23 (A5)
/A6: J4.B12 (A6), U8.2 (A1), Z1.B22 (A6)
/A7: J4.B13 (A7), U8.1 (A0), Z1.B21 (A7)
/A8: J4.A12 (A8), Z1.A26 (A8)
/A9: J4.A10 (A9), Z1.B27 (A9)
/A10: J4.A7 (A10), Z1.A27 (A10)
/A11: J4.A9 (A11), U2.11 (B7), Z1.B28 (A11)
/A12: J4.B14 (A12), U2.12 (B6), Z1.B2 (A12)
/A13: J4.A13, Z1.A2 (A13)
/A14: J4.A6 (A14), U3.4, Z1.B1 (A14)
/A15: J4.A14 (A15), U3.5, Z1.A1 (A15)
/BA14: J3.2 (C), J4.B17 (BA14)
/BA15: J4.B18 (BA15), U6.5 (Q1)
/BA16: J4.B19 (BA16), U6.6 (Q2)
/BA17: J4.B20 (BA17), U6.9 (Q3)
/BA18: J4.B21 (BA18), U6.12 (Q4)
/BANK0: U6.16 (Q6), U7.1 (A0)
/BANK1: U6.19 (Q7), U7.2 (A1)
/CARTRIDGE_EN: U3.9, U6.15 (Q5)
/D0: D16.2 (A), J4.B4 (D0), U6.3 (D0), Z1.A6 (D0)
/D1: D15.2 (A), J4.B3 (D1), U6.4 (D1), Z1.A7 (D1)
/D2: D14.2 (A), J4.B2 (D2), U6.7 (D2), Z1.A8 (D2)
/D3: D13.2 (A), J4.A1 (D3), U6.8 (D3), Z1.A11 (D3)
/D4: D12.2 (A), J4.A2 (D4), U6.13 (D4), Z1.A12 (D4)
/D5: J4.A3 (D5), U6.14 (D5), Z1.A10 (D5)
/D6: J4.A4 (D6), U6.17 (D6), Z1.A9 (D6)
/D7: J4.A5 (D7), U6.18 (D7), Z1.A3 (D7)
/OUT_31: U6.11 (Cp), U8.15 (O0)
/~IORQ: U3.2, U8.5 (E2), Z1.A17 (~IORQ)
/~M1: U8.6 (E3), Z1.A24 (~M1)
/~MREQ: J4.A8 (~MREQ), U7.5 (E2), Z1.A16 (~MREQ)
/~NMI: R13.2, Z1.A14 (~NMI)
/~RD: U3.13, Z1.A18 (~RD)
/~RESET: R11.2, U6.1 (~Mr), Z1.B20 (~RESET)
/~ROMCS: Q1.1 (E), Z1.B25 (~ROMCS)
/~ROM_0: J4.A18 (~ROM_0), U7.15 (O0)
/~ROM_1: J4.A19 (~ROM_1), U7.14 (O1)
/~ROM_2: J4.A20 (~ROM_2), U7.13 (O2)
/~ROM_3: J4.A21 (~ROM_3), U7.12 (O3)
/~ROM_OE: J4.A17 (~ROM_OE), U4.6
/~WR: U8.4 (E1), Z1.A19 (~WR)
EXROM: J4.B15 (EXROM), R12.2, U4.11
GND: C1.2, C2.2, C3.2, C4.2, C5.2, C6.2, C7.2, C8.2, J4.B1 (GND), J4.B22 (GND), R12.1, R14.1, SW1.1, SW2.1, U1.1 (A->B), U1.10 (GND), U2.1 (A->B), U2.10 (GND), U2.19 (CE), U3.7 (GND), U3.11, U4.7 (GND), U4.13, U6.10 (GND), U7.3 (A2), U7.4 (E1), U7.8 (GND), U8.8 (GND), Z1.B6 (GND), Z1.B7 (GND), Z1.B14 (GND)
unnamed: D1.1 (K), J1.1
unnamed: D1.2 (A), D10.2 (A), R1.2, U1.14 (B4)
unnamed: D2.1 (K), J1.6
unnamed: D2.2 (A), D9.2 (A), R4.2, U1.15 (B3)
unnamed: D3.1 (K), J1.2
unnamed: D3.2 (A), D8.2 (A), R3.2, U1.13 (B5)
unnamed: D4.1 (K), J1.3
unnamed: D4.2 (A), D7.2 (A), R2.2, U1.11 (B7)
unnamed: D5.1 (K), J1.4
unnamed: D5.2 (A), D6.2 (A), R5.2, U1.12 (B6)
unnamed: D6.1 (K), J2.1
unnamed: D7.1 (K), J2.6
unnamed: D8.1 (K), J2.2
unnamed: D9.1 (K), J2.3
unnamed: D10.1 (K), J2.4
unnamed: D11.1 (K), R14.2
unnamed: D12.1 (K), U1.5 (A3)
unnamed: D13.1 (K), U1.6 (A4)
unnamed: D14.1 (K), U1.7 (A5)
unnamed: D15.1 (K), U1.8 (A6)
unnamed: D16.1 (K), U1.9 (A7)
unnamed: J1.8 (GND), U2.9 (A7)
unnamed: J2.8 (GND), U2.8 (A6)
unnamed: J3.1 (A), U6.2 (Q0)
unnamed: J5.1 (A), U4.2
unnamed: J5.2 (C), U1.19 (CE)
unnamed: Q1.2 (B), R15.1
unnamed: R11.1, SW1.2
unnamed: R13.1, SW2.2
unnamed: R15.2, U3.8, U4.9, U7.6 (E3)
unnamed: U3.3, U4.8
unnamed: U3.6, U4.5
unnamed: U3.10, U4.10
unnamed: U3.12, U4.1
OUT_63: J4.A22 (~OUT_63), U8.11 (O4)
VCC: C1.1, C2.1, C3.1, C4.1, C5.1, C6.1, C7.1, C8.1, D11.2 (A), J3.3 (B), J4.A15 (VCC), J5.3 (B), Q1.3 (C), R1.1, R2.1, R3.1, R4.1, R5.1, U1.20 (VCC), U2.20 (VCC), U3.14 (VCC), U4.14 (VCC), U6.20 (VCC), U7.16 (VCC), U8.16 (VCC), Z1.B3 (+5v)

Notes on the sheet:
/ROM_CS is an enable for the internal ZX Spectrum ROM. Bring high to use cartridge.
Sinclair Interface 2 joystick interface, it has the original Atari-style pinout (because no one wants to use an SJS or even have one that still works).
Allows the user to boot from a different 16K ROM image via jumper. Mainly useful for having different diagnostic image available.

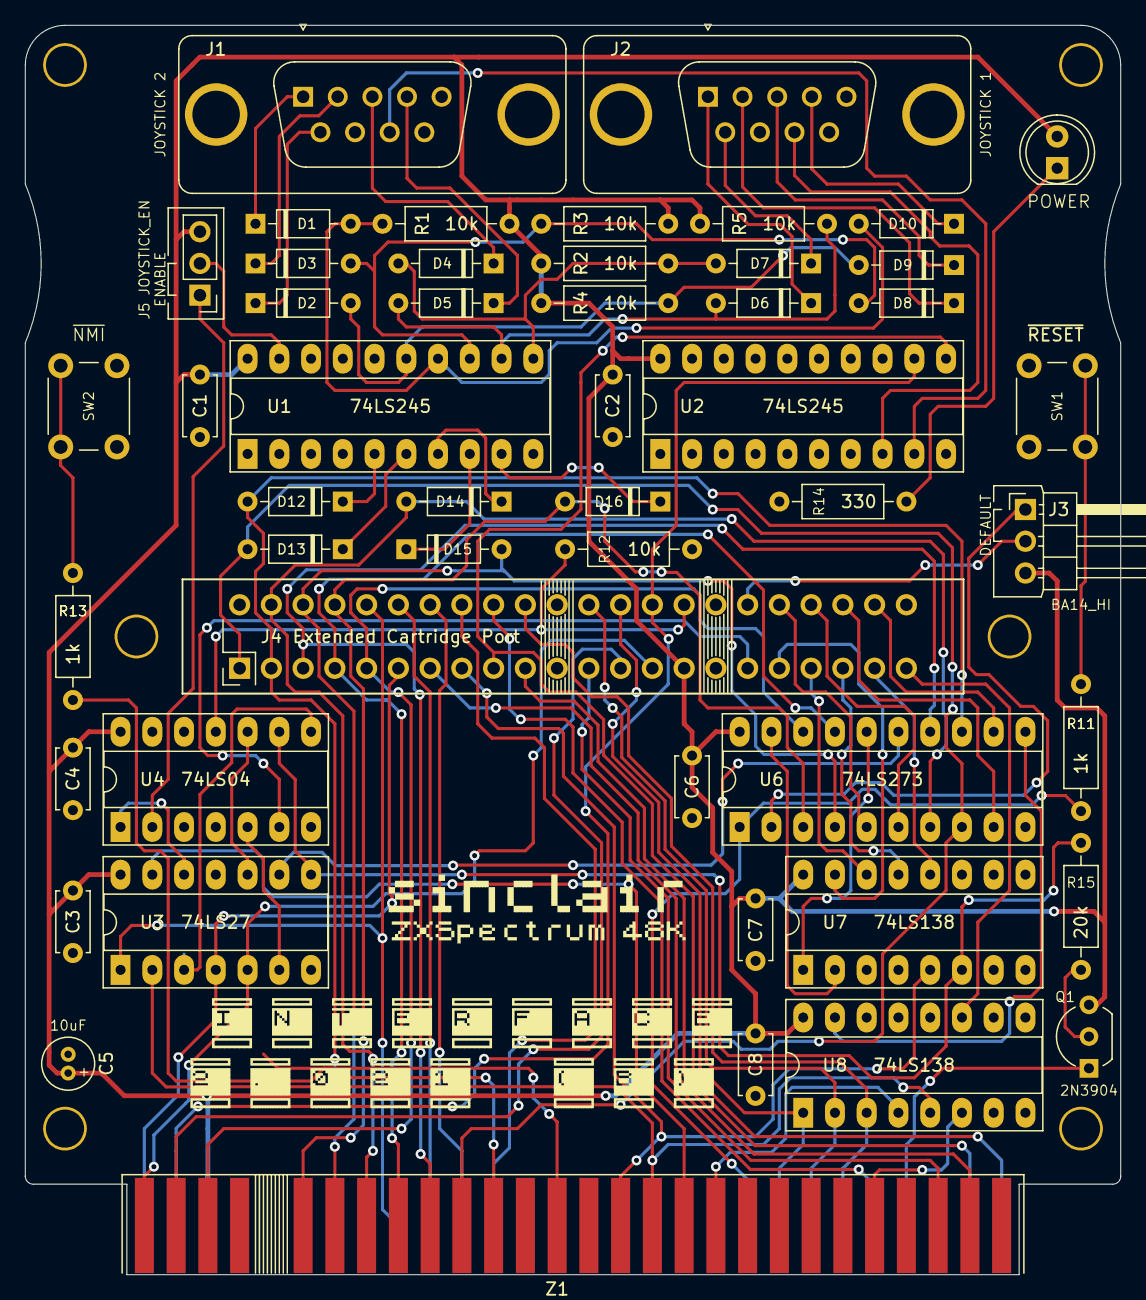
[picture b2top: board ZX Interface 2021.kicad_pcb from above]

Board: 2 copper layers, 87.6 x 99.9 mm, 58 parts (0 on the bottom side), 84 nets.

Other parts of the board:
sinclair_title: Val**; interface_2021
sinclair_title#2: sinclair_title

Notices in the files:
ZX Cartridge 1983/ZX Cartridge 1983.kicad_pcb:
Licensed under
CERN OHL v1.2
